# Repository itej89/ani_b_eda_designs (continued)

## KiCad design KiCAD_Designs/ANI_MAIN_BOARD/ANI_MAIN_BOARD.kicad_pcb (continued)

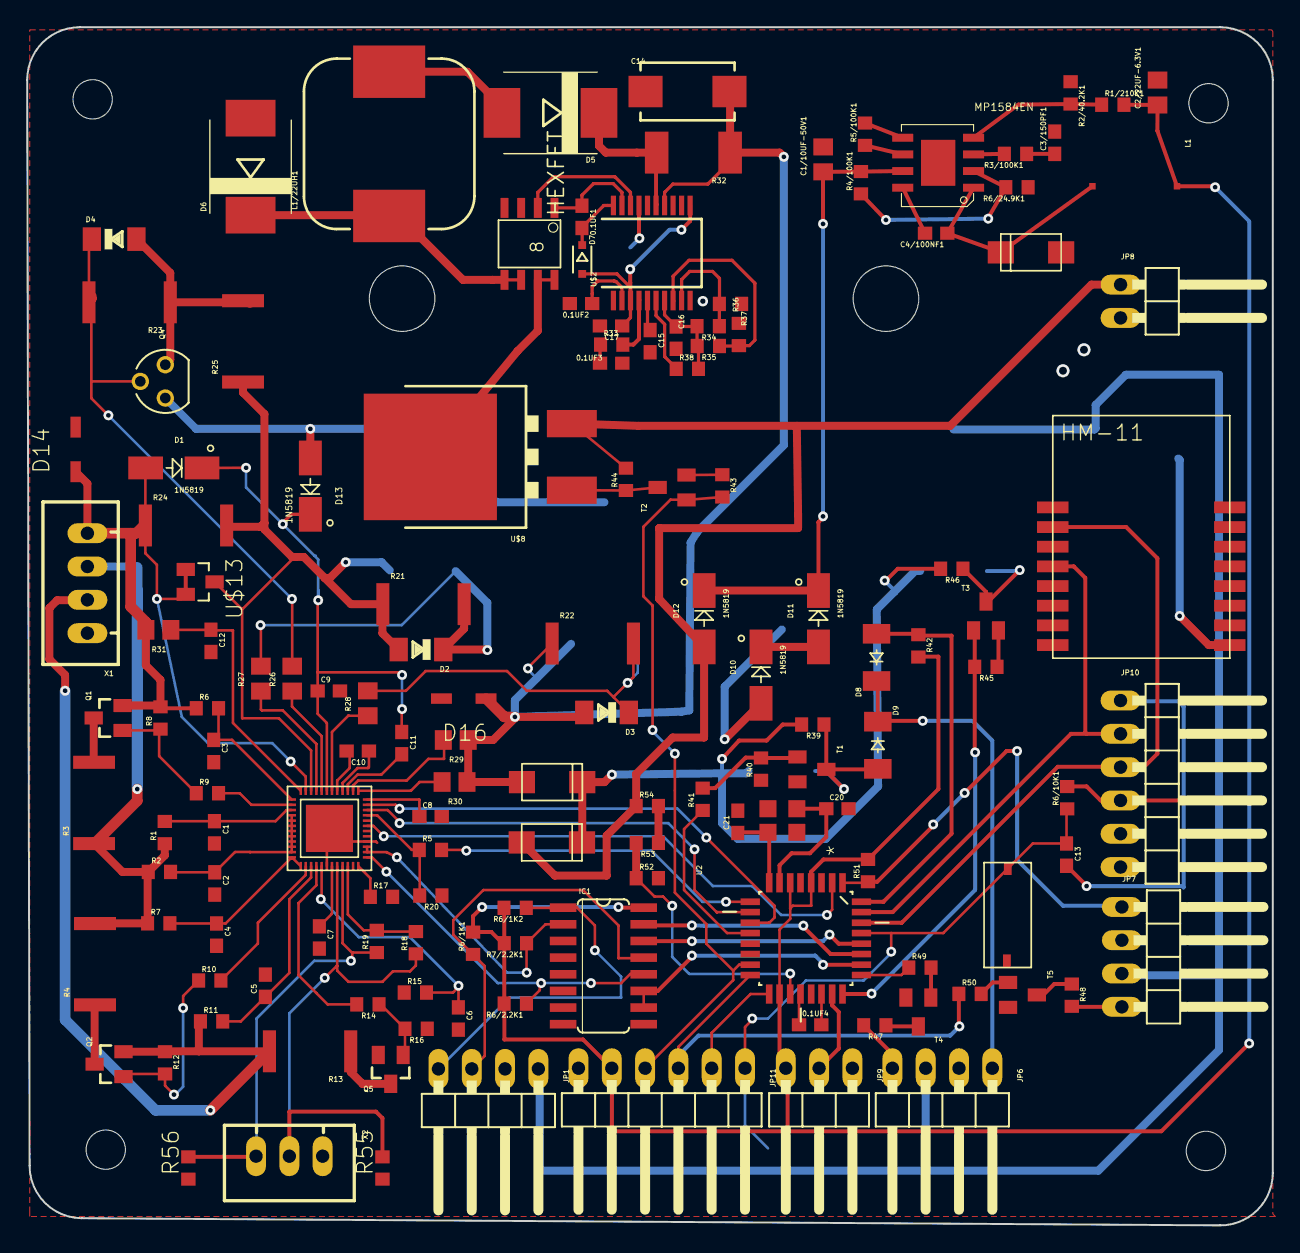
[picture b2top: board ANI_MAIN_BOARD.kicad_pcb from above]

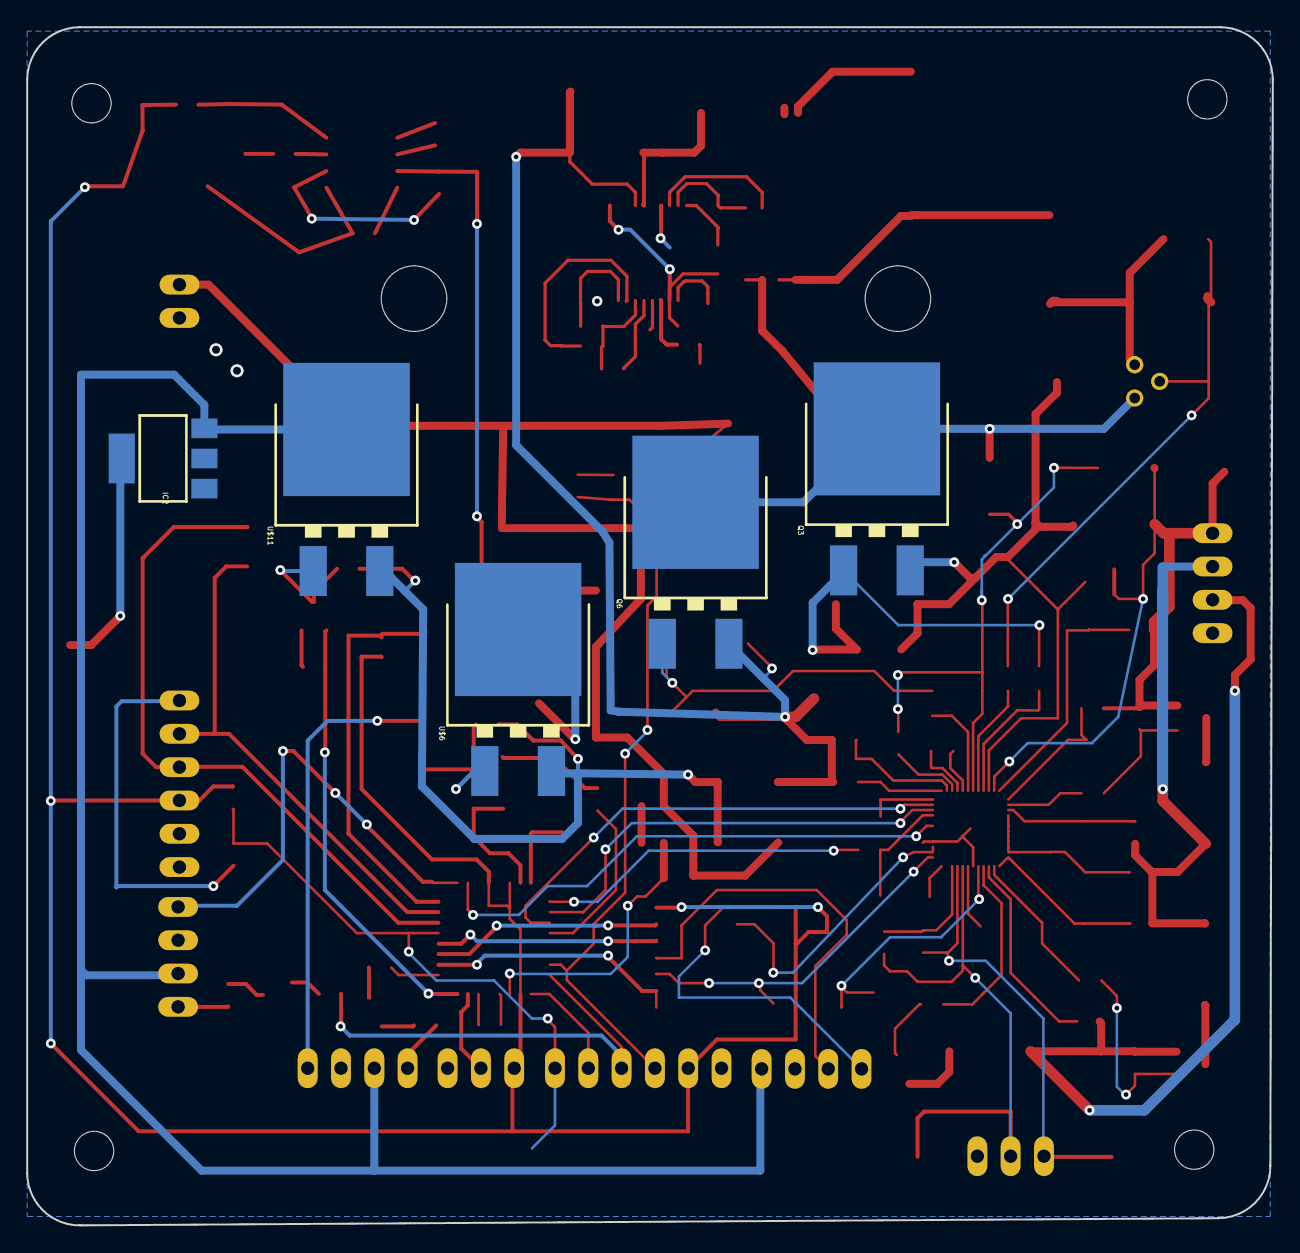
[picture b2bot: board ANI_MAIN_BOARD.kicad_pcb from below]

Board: 2 copper layers, 95.0 x 91.4 mm, 154 parts (5 on the bottom side), 113 nets.

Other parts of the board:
@HOLE0, @HOLE1, @HOLE2, @HOLE3, @HOLE4, @HOLE5: (no value)

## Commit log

2024-08-31 Initial Commit.
